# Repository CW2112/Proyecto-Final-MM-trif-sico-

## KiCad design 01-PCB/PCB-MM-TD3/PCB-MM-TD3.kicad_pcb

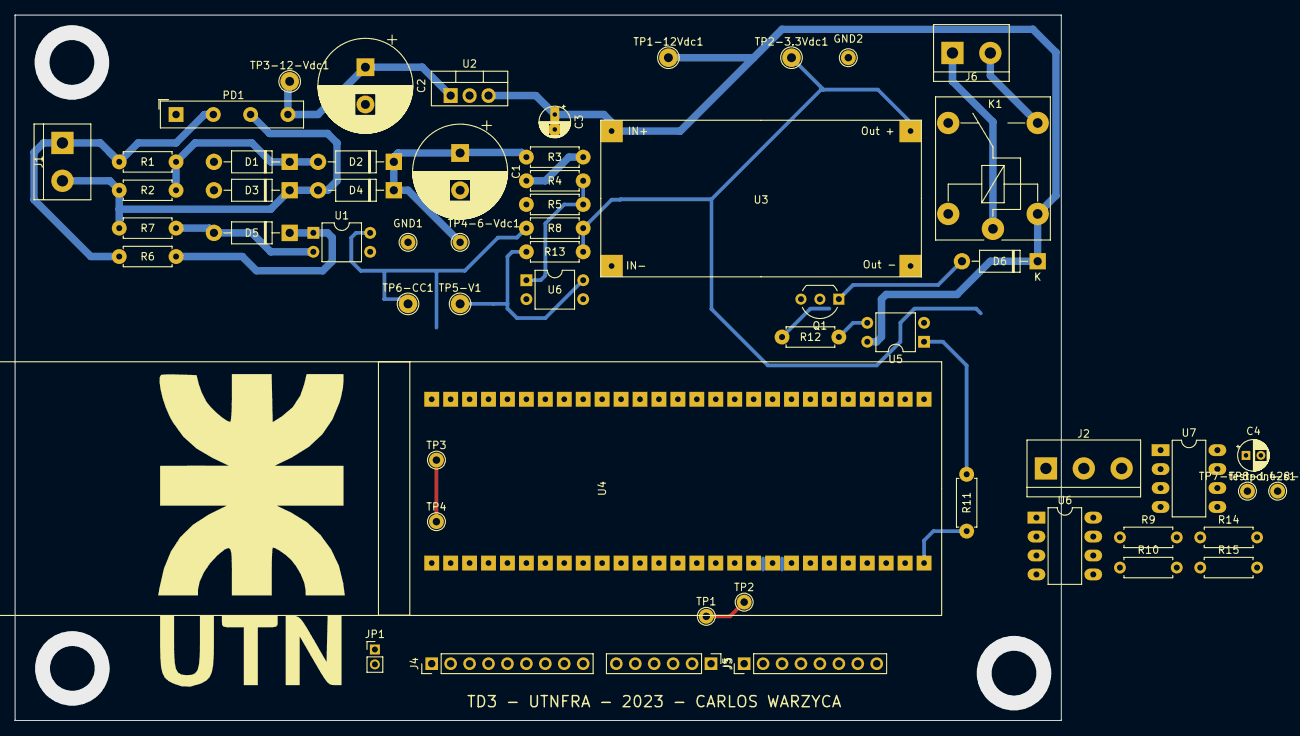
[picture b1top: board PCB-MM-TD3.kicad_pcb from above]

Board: 2 copper layers, 140.3 x 94.6 mm, 57 parts (0 on the bottom side), 45 nets.

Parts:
C1, C2: 470uf; CP_Radial_D12.5mm_P5.00mm
C3, C4: 10uf; CP_Radial_D4.0mm_P2.00mm
D1, D2, D3, D4, D5, D6: 1N4007; D_DO-41_SOD81_P10.16mm_Horizontal
GND1, GND2: TestPoint; TestPoint_THTPad_D2.0mm_Drill1.0mm
J1: IN-AC; TerminalBlock_bornier-2_P5.08mm
J2: In_sens; TerminalBlock_bornier-3_P5.08mm
J3: SD_Mem; PinHeader_1x06_P2.54mm_Vertical
J4: TFT_Screen; PinHeader_1x09_P2.54mm_Vertical
J5: Keyboard; PinHeader_1x08_P2.54mm_Vertical
J6: Out-Contactor; TerminalBlock_bornier-2_P5.08mm
JP1: Jumper; PinHeader_1x02_P2.00mm_Vertical
K1: FINDER-36.11; Relay_SPDT_Finder_36.11
PD1: KBL02-3A; Diode_Bridge_19.0x3.5x10.0mm_P5.0mm
Q1: BC547; TO-92_Inline_Wide
R1, R2, R6, R7: 4,7K; R_Axial_DIN0207_L6.3mm_D2.5mm_P7.62mm_Horizontal
R3, R5, R8: 10K; R_Axial_DIN0207_L6.3mm_D2.5mm_P7.62mm_Horizontal
R4: 22K; R_Axial_DIN0207_L6.3mm_D2.5mm_P7.62mm_Horizontal
R9: 10k; R_Axial_DIN0207_L6.3mm_D2.5mm_P7.62mm_Horizontal
R10: 4,7k; R_Axial_DIN0207_L6.3mm_D2.5mm_P7.62mm_Horizontal
R11: 1K; R_Axial_DIN0207_L6.3mm_D2.5mm_P7.62mm_Horizontal
R12: 510; R_Axial_DIN0207_L6.3mm_D2.5mm_P7.62mm_Horizontal
R13, R15: 30K; R_Axial_DIN0207_L6.3mm_D2.5mm_P7.62mm_Horizontal
R14: 100; R_Axial_DIN0207_L6.3mm_D2.5mm_P7.62mm_Horizontal
TP1, TP2, TP3, TP4, TP4-6-Vdc1, TP8-1,428-Vdc1: TestPoint; TestPoint_THTPad_D2.0mm_Drill1.0mm
TP1-12Vdc1, TP2-3.3Vdc1, TP3-12-Vdc1, TP5-V1, TP6-CC1: TestPoint; TestPoint_THTPad_D2.5mm_Drill1.2mm
TP7-testpont-s1: Test.point-Sen; TestPoint_THTPad_D2.0mm_Drill1.0mm
U1, U5, U6: PC817; DIP-4_W7.62mm
U2: LM7812_TO220; TO-220-3_Vertical
U3: Fuente_3.3Vcc; Fuente Reg DC-DC
U4: LPC1769-Board
U6#2: IL300; DIP-8_W7.62mm_LongPads
U7: LM201; DIP-8_W7.62mm_LongPads

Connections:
3.3Vcc: J3.5, JP1.2, R8.1, R9.1, TP2-3.3Vdc1.1, U3.3, U6.4, U6#2.6
6Vcc: C1.1, D2.1, D4.1, R3.2, TP4-6-Vdc1.1, U6#2.3, U7.7
12Vcc: C3.1, D6.1, K1.A1, TP1-12Vdc1.1, U2.3, U3.1, U5.4
AD-In: J2.2, TP7-testpont-s1.1, U4.17
AD-Vcc: R13.1, TP5-V1.1, U4.16, U6.3, U6#2.5
Act-Contact: R11.1, U4.27
CruceCero: R8.2, TP6-CC1.1, U1.4, U4.15
DC_RSR: J4.5, U4.9
GND: C2.2, C3.2, C4.2, GND2.1, J2.3, J3.6, J4.7, J4.8, PD1.1, Q1.3, R10.2, R13.2, U1.3, U2.2, U3.2, U3.4, U4.1, U4.54, U5.2
GND1: C1.2, D1.2, D3.2, GND1.1, R5.2, R15.2, U6.2, U6#2.1, U7.4, U7.5
Key-C1: J5.5, U4.22
Key-C2: J5.6, U4.23
Key-C3: J5.7, U4.24
Key-C4: J5.8, U4.25
Key-F1: J5.1, U4.18
Key-F2: J5.2, U4.19
Key-F3: J5.3, J5.4, U4.20, U4.21
MISO_1: J4.2, U4.6
MISO_2: J3.2, TP1.1, TP2.1, U4.12
MOSI_1: J4.1, U4.5
MOSI_2: J3.1, U4.11
unnamed: C2.1, PD1.4, TP3-12-Vdc1.1, U2.1
unnamed: C4.1, J2.1, R9.2, R10.1
unnamed: D1.1, D2.2, R1.1, R2.1
unnamed: D3.1, D4.2, J1.2, PD1.3, R2.2, R7.2
unnamed: D5.1, R6.1, U1.1
unnamed: D5.2, R7.1, U1.2
unnamed: D6.2, K1.A2, Q1.1
unnamed: J1.1, PD1.2, R1.2, R6.2
unnamed: J6.1, K1.11
unnamed: J6.2, K1.14
unnamed: JP1.1, TP3.1, TP4.1, U4.28
unnamed: Q1.2, R12.1
unnamed: R3.1, R4.2
unnamed: R4.1, R5.1, TP8-1,428-Vdc1.1, U6.1, U7.3
unnamed: R11.2, U5.1
unnamed: R12.2, U5.3
unnamed: R14.1, U6#2.2
unnamed: R14.2, U7.6
unnamed: R15.1, U6#2.4, U7.2
ResetTFT: J4.6, U4.10
SCK_1: J4.3, U4.7
SCK_2: J3.3, U4.13
SSEL_1: J4.4, U4.8
SSEL_2: J3.4, U4.14

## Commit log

2026-03-29 primera emision PCB
2026-03-29 presentacion proyecto
2026-03-29 hojas de datos
2026-03-29 Simulaciones
2026-03-29 Programa
